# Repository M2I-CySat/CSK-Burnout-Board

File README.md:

## Power distribution board for CySat

This board contains the components to go from 3.3v to 8v and the MOSFETS for controlling the antenna deployment

## Boost Board files (from CySat-1-Main)

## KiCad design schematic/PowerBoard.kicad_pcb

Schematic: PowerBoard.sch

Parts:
C1: 470uF; CP_Elec_8x10.5
C2, C7: 10uF; C_0805
C3: 2.2nF; C_0805
C4: 1uF; C_0805
C5: 47pF; C_0805
C6: 10nF; C_0805
C8: 470uF; CP_Elec_8x10
D1: SS34; D_SMC
D2, D3: LED; LED_0805
H1, H2: CONN_02X26; CSK_Header
J1, J2: ToResistor; Pin_Header_Straight_1x02_Pitch2.54mm
J3: I2C_Debug; Socket_Strip_Angled_1x02_Pitch2.54mm
L1: 6.8uH; L_0805
Q1, Q2: IRLB8721PBF; SOT-666
R1: 53k; R_0805
R2: 10k; R_0805
R3: 51k; R_0805
R4, R5: 51; R_0805
U1: PAM2423A; HTSOP-8-1EP_3.9x4.9mm_Pitch1.27mm

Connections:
+3V3: H2.27, H2.28
+5V: C1.1, C2.1, C4.2, H1.32, H1.47, H2.25, H2.26, J1.2, J2.2, L1.1, U1.2, U1.3
+8V: C7.1, C8.1, D1.1 (K), H2.19, H2.20, R1.1
GND: C1.2, C2.2, C3.2, C4.1, C5.2, C6.1, C7.2, C8.2, D2.1 (K), D3.1 (K), H2.9, H2.14, H2.17, H2.21, H2.22, H2.29, H2.30, H2.32, H2.47, H2.48, Q1.3 (S), Q2.3 (S), R2.2, U1.1, U1.8
I2C_SCL: H1.43, J3.2
I2C_SDA: H1.41, J3.1
LineDeploymentDevice: J2.1, Q2.2 (D)
unnamed: C3.1, R3.2
unnamed: C5.1, R3.1, U1.4
unnamed: C6.2, U1.6
unnamed: D1.2 (A), L1.2, U1.5
unnamed: D2.2 (A), R4.2
unnamed: D3.2 (A), R5.2
unnamed: R1.2, R2.1, U1.7
Pri_Deploy: H1.1, H2.1, Q1.1 (G), Q2.1 (G), R4.1, R5.1
SecondaryLineDeploymentDevice: J1.1, Q1.2 (D)

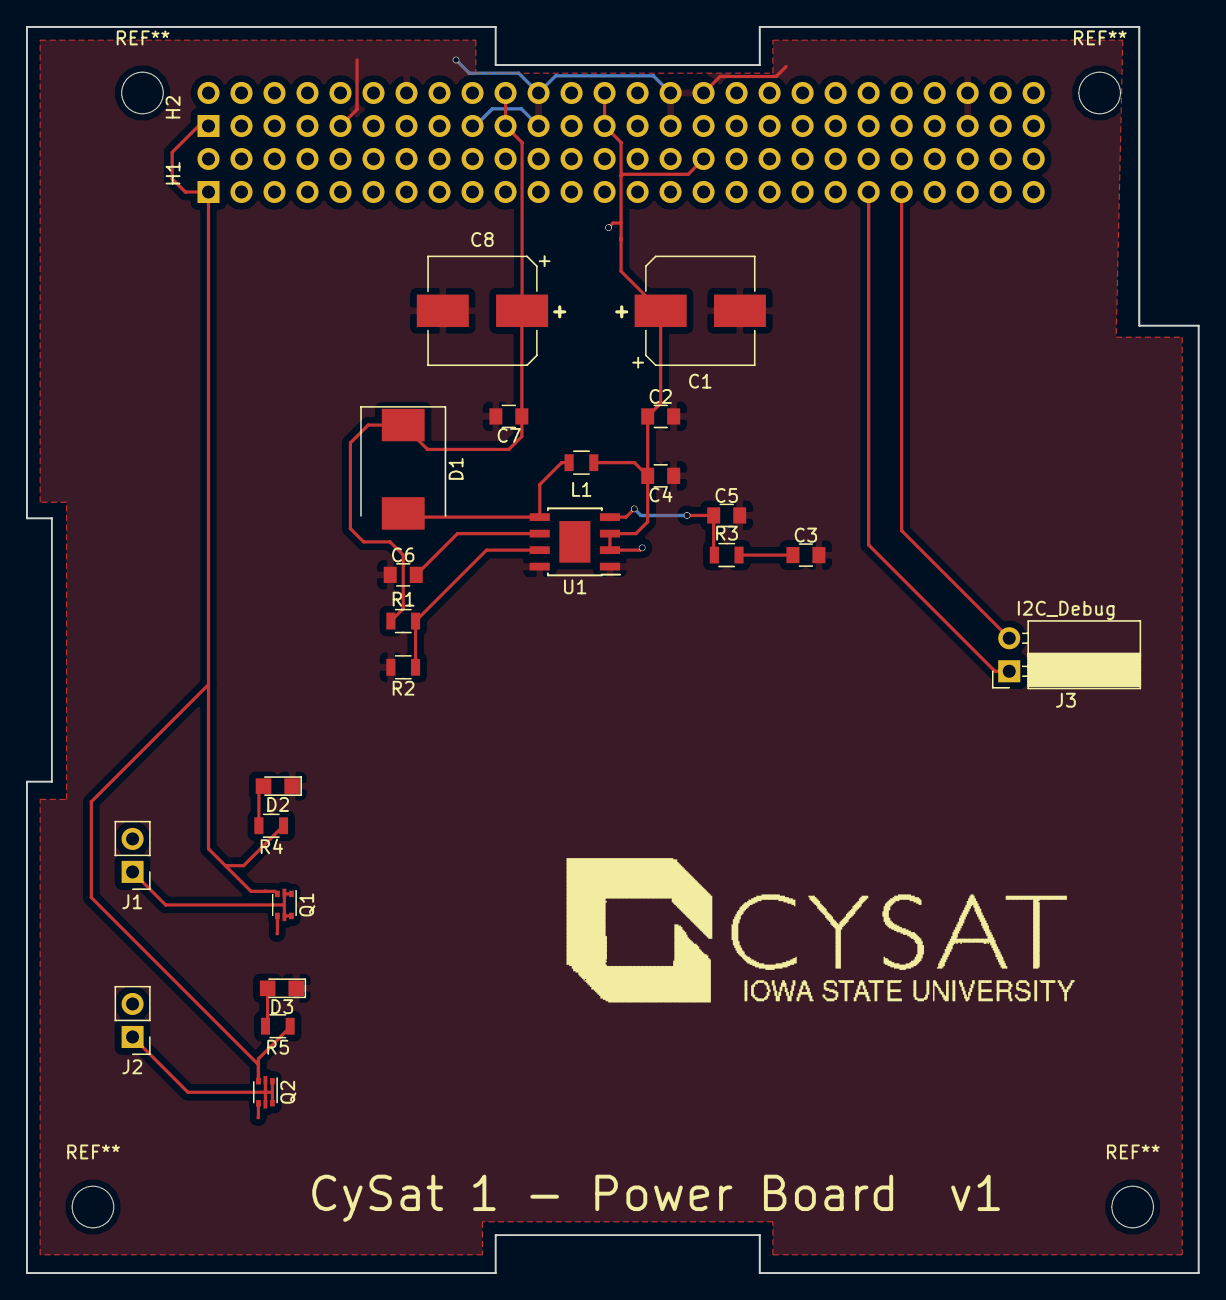
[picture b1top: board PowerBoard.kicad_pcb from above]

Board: 2 copper layers, 90.2 x 95.9 mm, 26 parts (0 on the bottom side), 16 nets.

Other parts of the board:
LOGO: LOGO

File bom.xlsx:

Code | Value | Quantity | Link | Notes
C1,C8 | 470uF | 2 | https://www.digikey.com/product-detail/en/panasonic-electron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
C2,C7 | 10uF | 2 | https://www.digikey.com/product-detail/en/vishay-sprague/293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
C3 | 2.2nF | 1 | https://www.digikey.com/product-detail/en/kemet/C0805C222KAR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
C4 | 1uF | 1 | https://www.digikey.com/product-detail/en/samsung-electro-me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
C5 | 47pF | 1 | https://www.digikey.com/product-detail/en/samsung-electro-me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
C6 | 10nF | 1 | https://www.digikey.com/product-detail/en/samsung-electro-me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
D1 |  | 1 | https://www.digikey.com/product-detail/en/on-semiconductor/S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
L1 | 6.8uH | 1 | https://www.digikey.com/product-detail/en/tdk-corporation/ML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 | Is 1A sufficient?
R1 | 53k | 1 | https://www.mouser.com/ProductDetail/Vishay/TNPW080553K0BEEN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
R2 | 10k | 1 | On hand
Q1 | N-CH 20V 1A | 1 | https://www.digikey.com/product-detail/en/central-semiconduc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

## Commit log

2018-06-22 Initial commit - Schematic finished
2018-06-22 Added folders, datasheets, and readme
2018-06-28 Added mosfet
2018-06-29 Started Schematic
2018-06-30 Create TODO
2018-07-02 Completed pcb design
2018-07-03 Playing with via values to get advanced circuits to take it
2018-07-06 Update check
2018-07-20 Fixed gerber files
2018-07-27 Cleaning up
2018-07-27 Scaled image
2018-07-28 Fixed PC104 conflicts and added i2c debug
2018-07-28 added zip
2018-07-30 Added names
2023-04-22 Move boost board from main to here
